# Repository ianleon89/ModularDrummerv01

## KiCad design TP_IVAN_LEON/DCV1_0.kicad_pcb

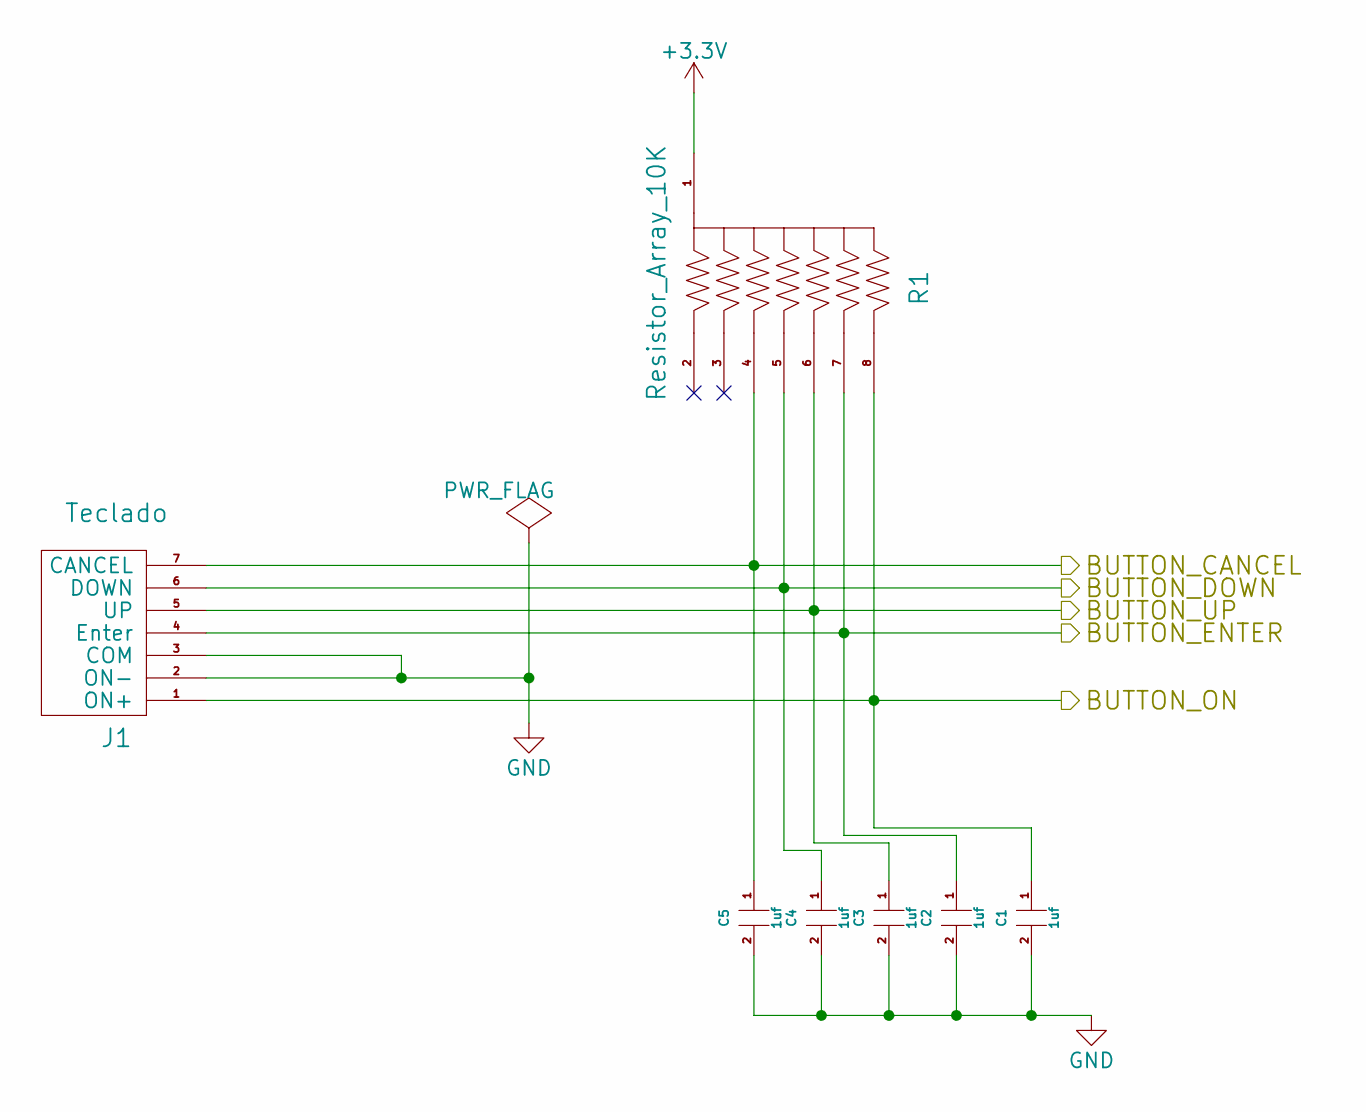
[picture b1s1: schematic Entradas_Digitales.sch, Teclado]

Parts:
C1, C2, C3, C4, C5: 1uf; c_1206; Digikey# 399-1254-2-ND
J1: Teclado; Connector_Molex_PicoBlade_53047-0810; Digikey# WM1737-ND
R1: Resistor_Array_10K; Resistor_Array_SIP8; Digikey# Y1747V0201BA0W-ND

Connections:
+3V3: R1.1; also elsewhere on the board
/Teclado/BUTTON_CANCEL: C5.1, J1.7 (CANCEL), R1.4; also elsewhere on the board
/Teclado/BUTTON_DOWN: C4.1, J1.6 (DOWN), R1.5; also elsewhere on the board
/Teclado/BUTTON_ENTER: C2.1, J1.4 (Enter), R1.7; also elsewhere on the board
/Teclado/BUTTON_ON: C1.1, J1.1 (ON+), R1.8; also elsewhere on the board
/Teclado/BUTTON_UP: C3.1, J1.5 (UP), R1.6; also elsewhere on the board
GND: C1.2, C2.2, C3.2, C4.2, C5.2, J1.2 (ON-), J1.3 (COM); also elsewhere on the board

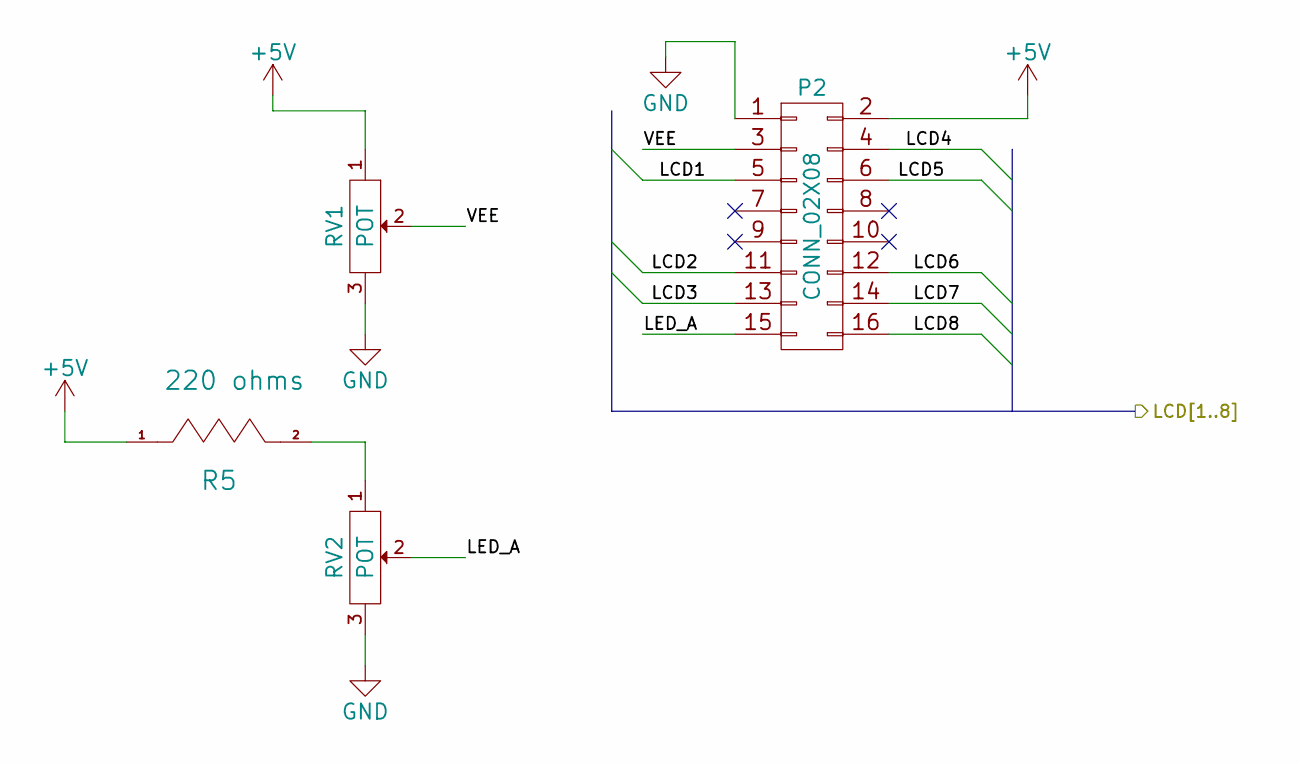
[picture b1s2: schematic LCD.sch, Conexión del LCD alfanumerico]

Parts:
P2: CONN_02X08; Pin_Header_Straight_2x08; Digikey# 952-2268-ND
R5: 220 ohms; Resistor_SMD+THTuniversal_1206_RM10_HandSoldering; Digikey# ERJ-T08J221V-ND
RV1, RV2: POT; Connector_Molex_PicoBlade_53047-0310; Digikey# WM1732-ND

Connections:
+5V: P2.2, R5.1, RV1.1; also elsewhere on the board
/Graphic_Interface/LCD1: P2.5; also elsewhere on the board
/Graphic_Interface/LCD2: P2.11; also elsewhere on the board
/Graphic_Interface/LCD3: P2.13; also elsewhere on the board
/Graphic_Interface/LCD4: P2.4; also elsewhere on the board
/Graphic_Interface/LCD5: P2.6; also elsewhere on the board
/Graphic_Interface/LCD6: P2.12; also elsewhere on the board
/Graphic_Interface/LCD7: P2.14; also elsewhere on the board
/Graphic_Interface/LCD8: P2.16; also elsewhere on the board
/Graphic_Interface/LED_A: P2.15, RV2.2
/Graphic_Interface/VEE: P2.3, RV1.2
GND: P2.1, RV1.3, RV2.3; also elsewhere on the board
unnamed: R5.2, RV2.1

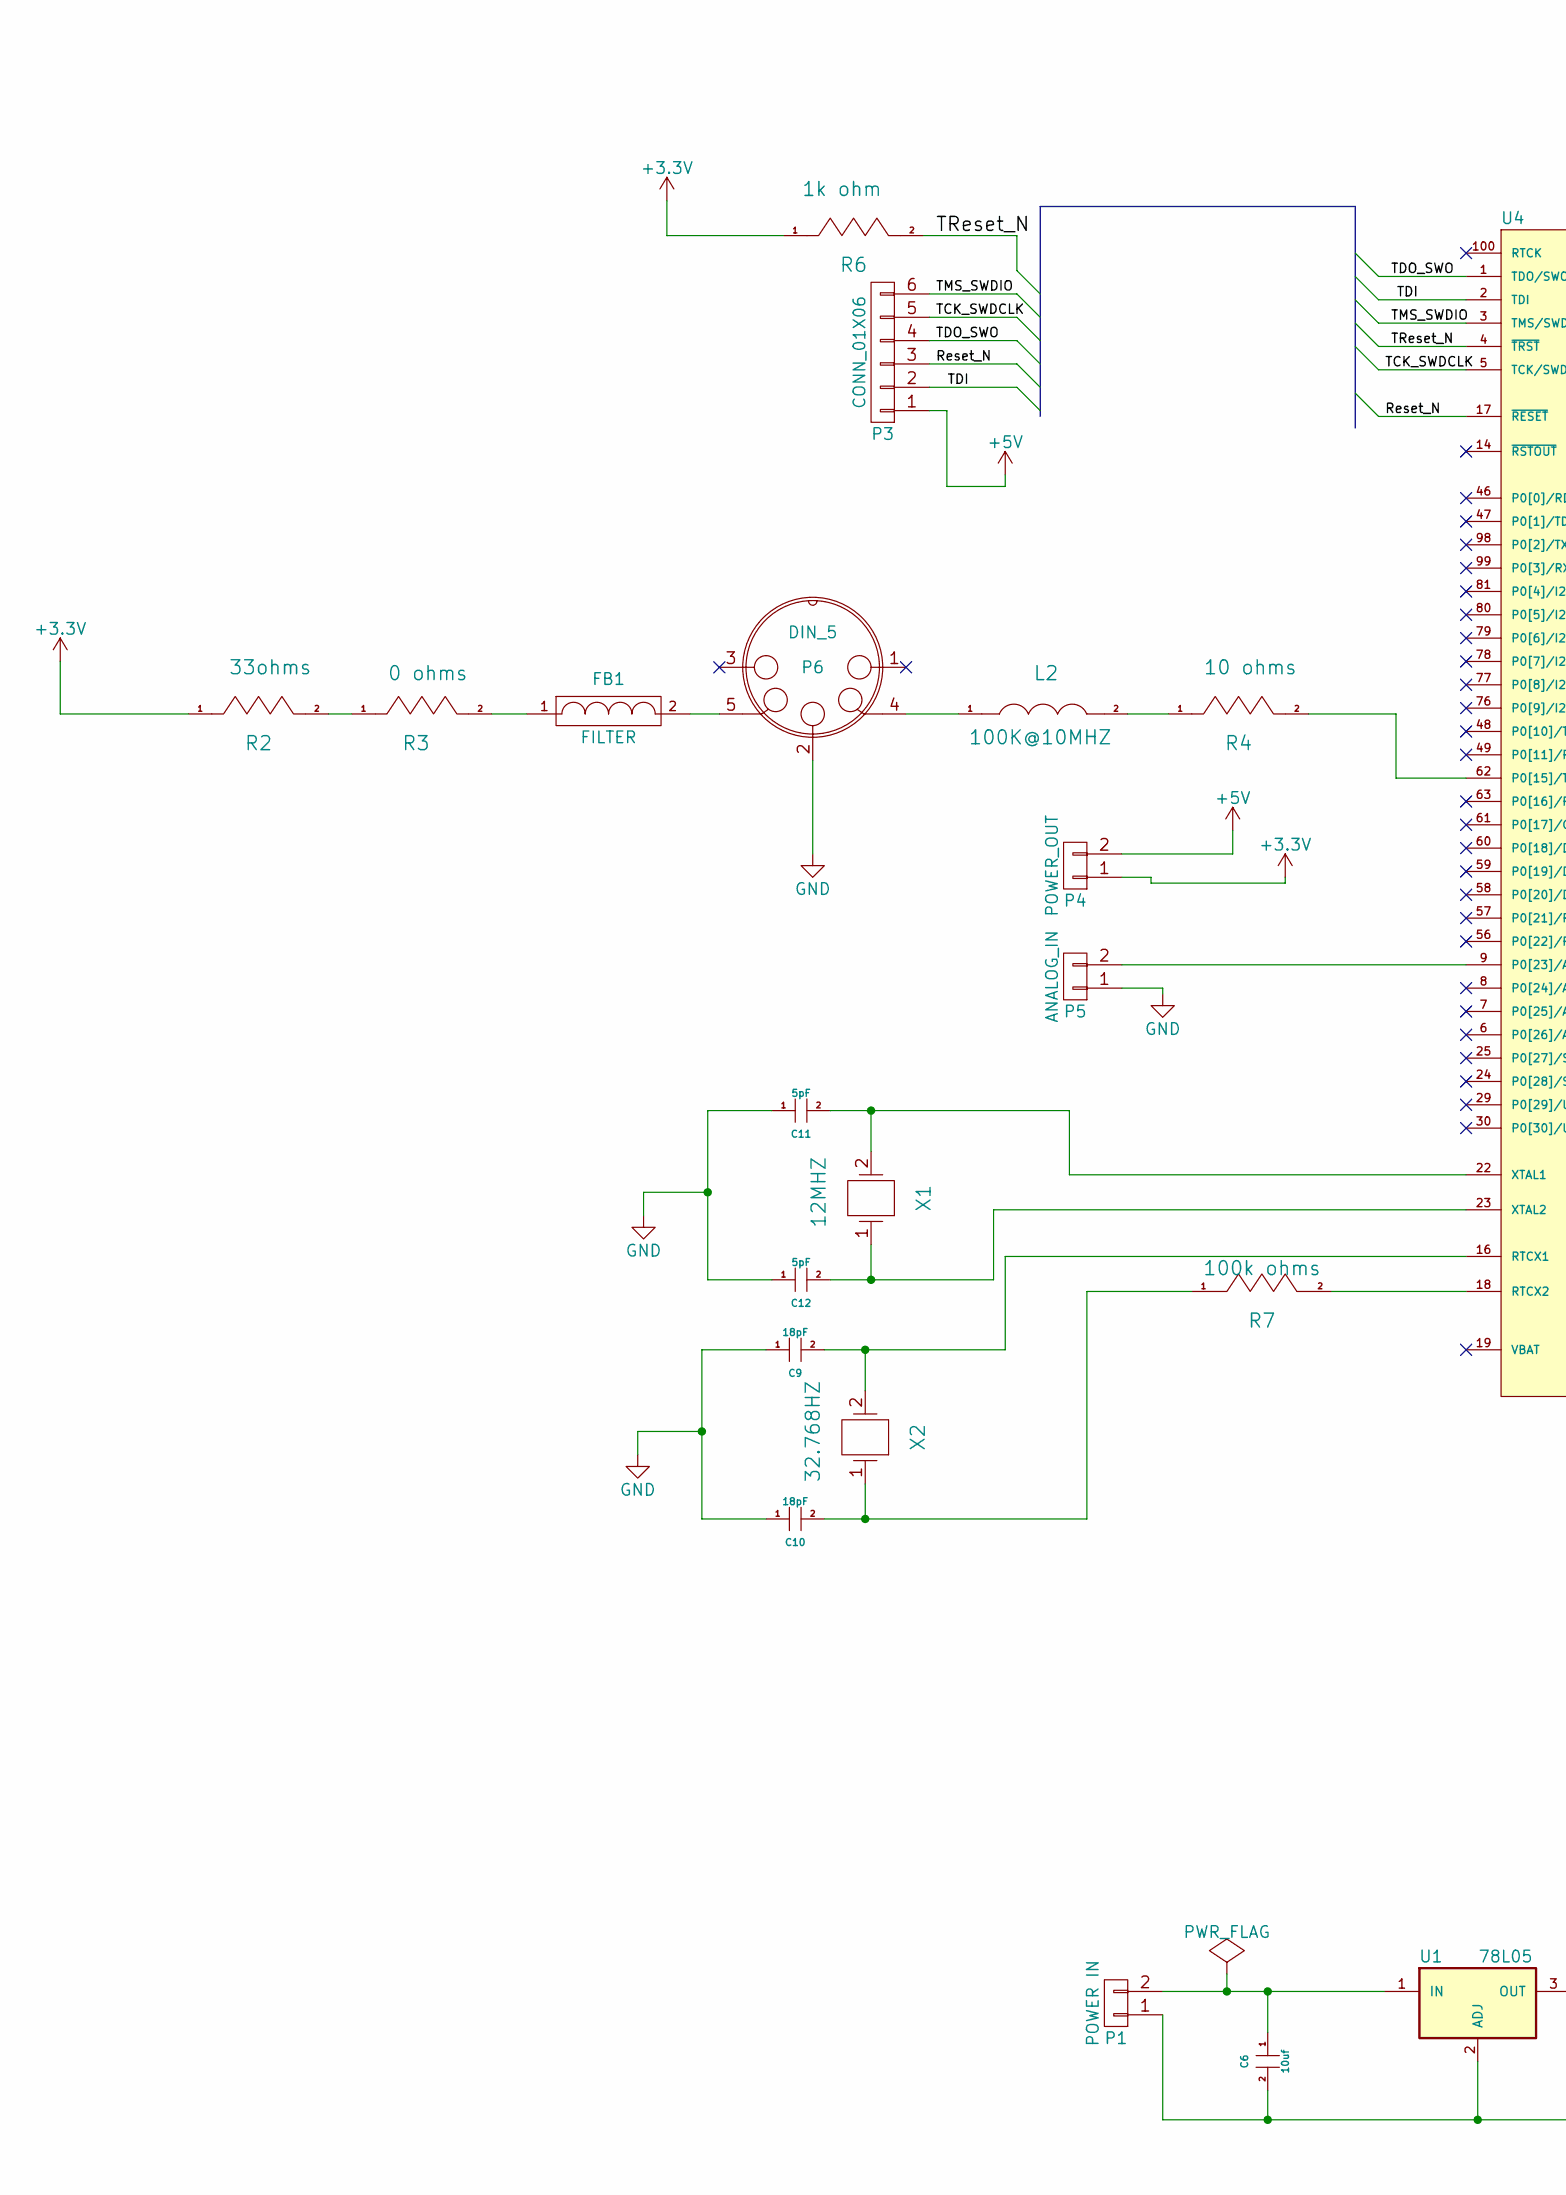
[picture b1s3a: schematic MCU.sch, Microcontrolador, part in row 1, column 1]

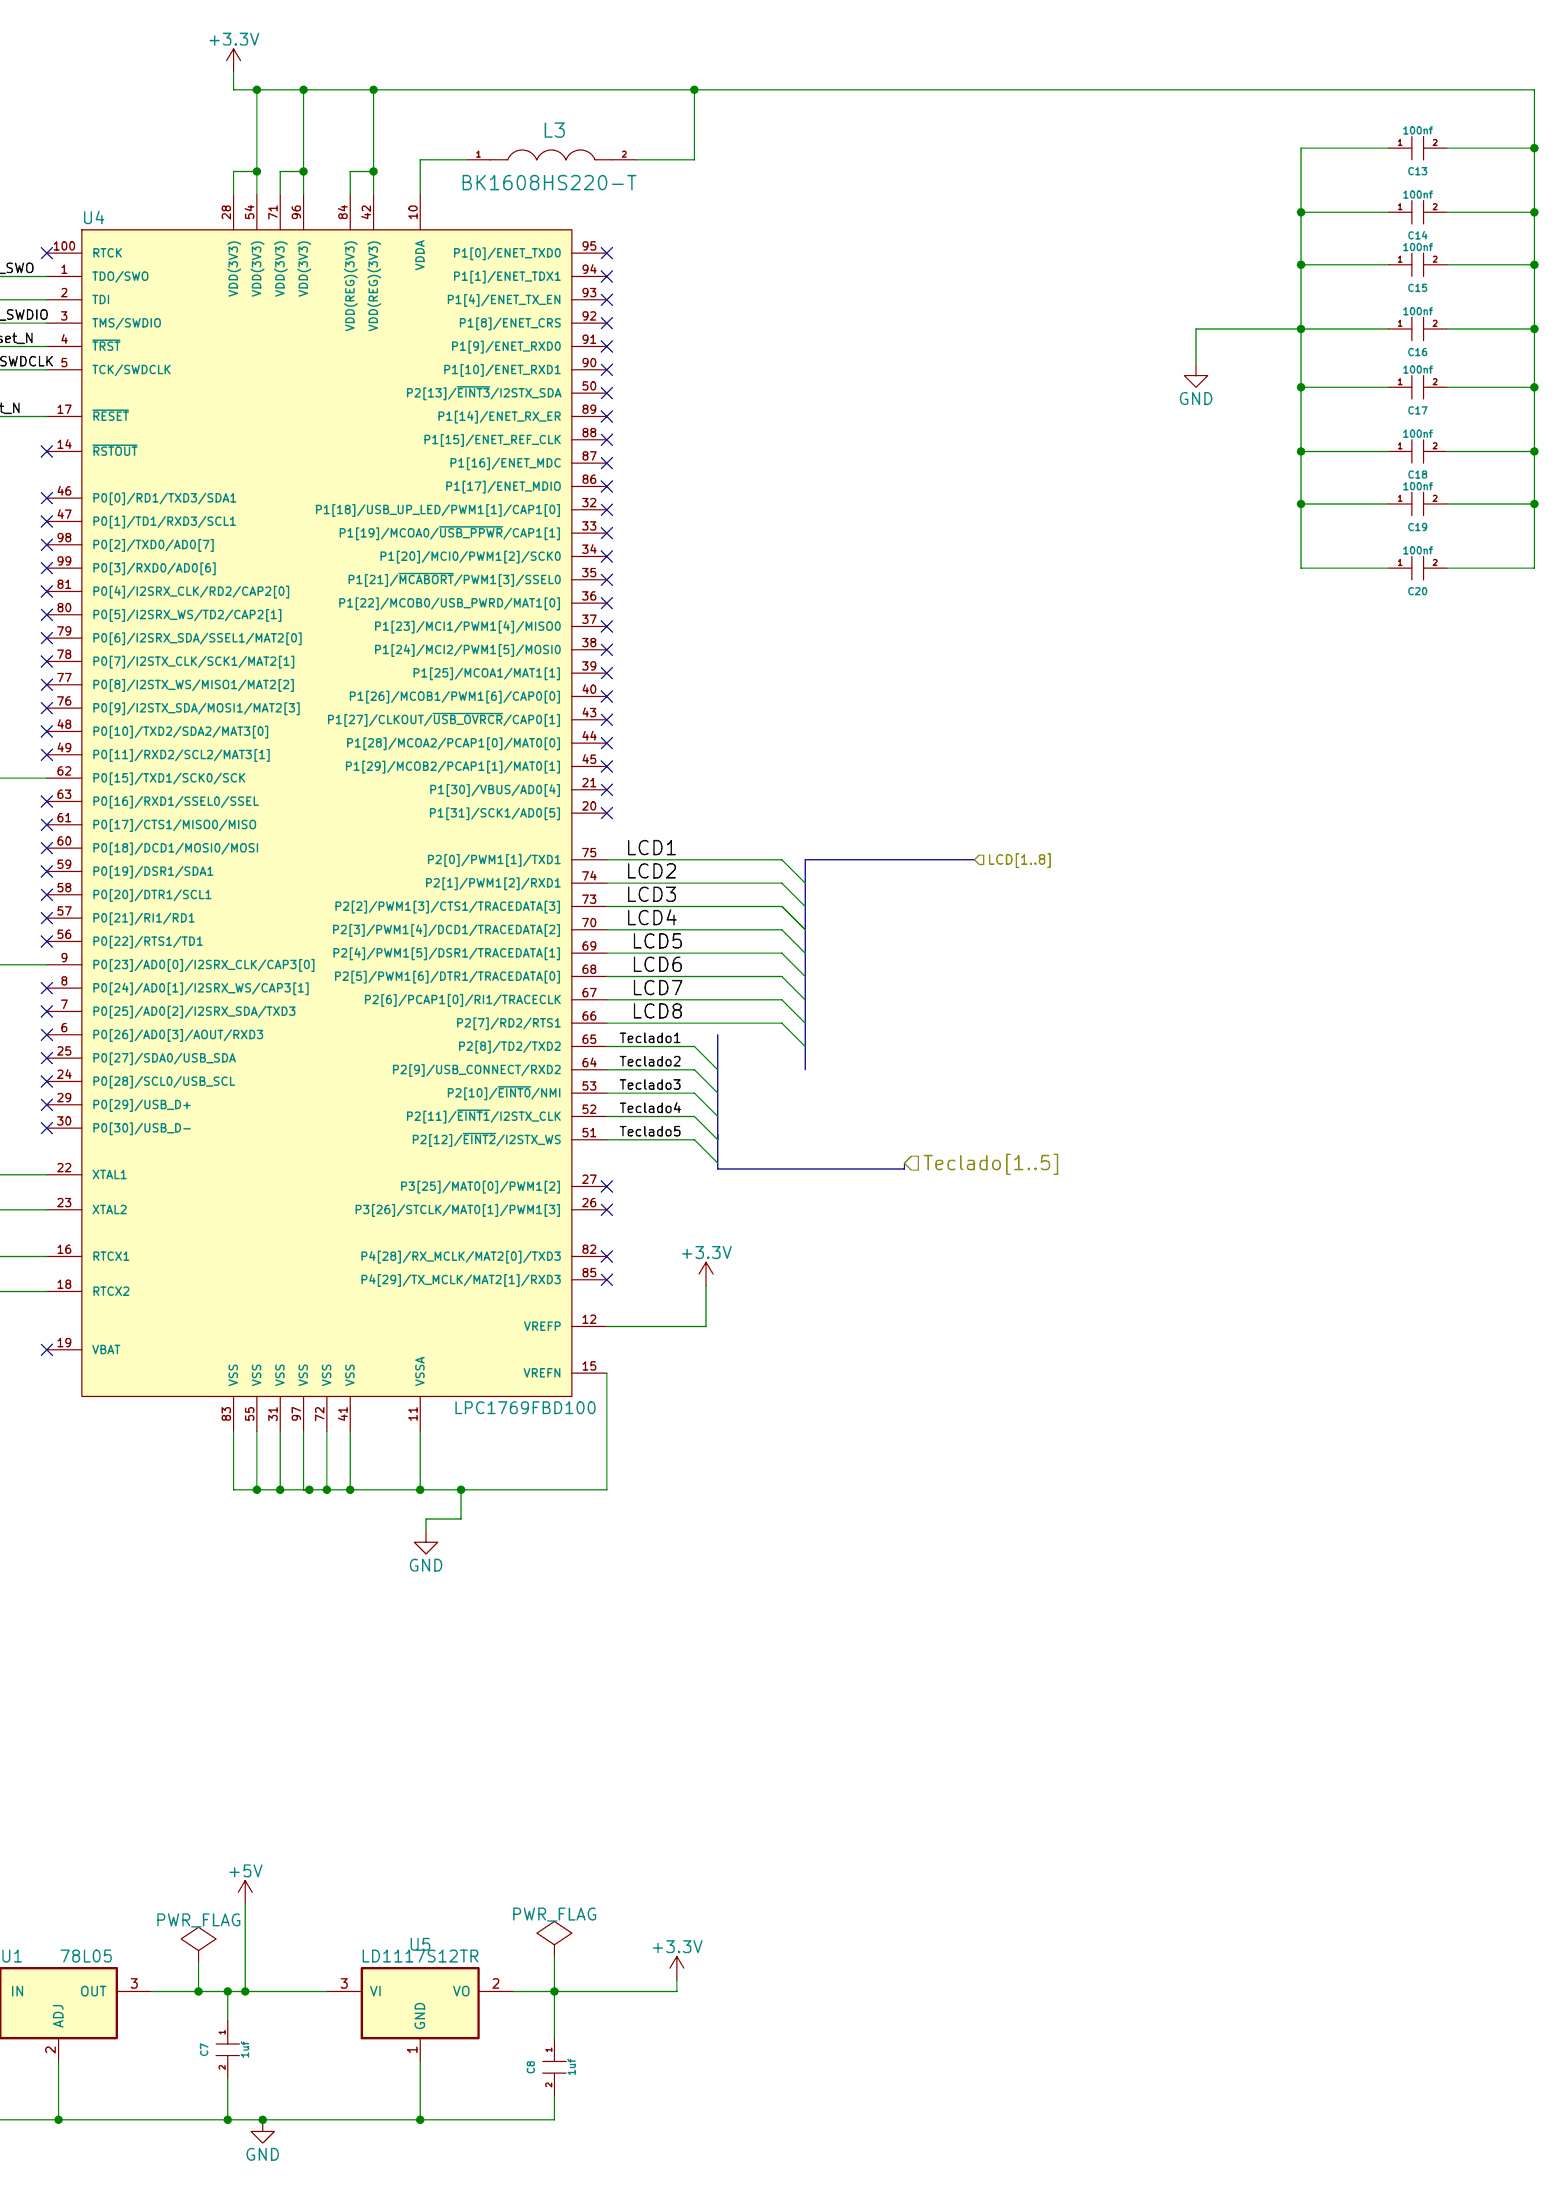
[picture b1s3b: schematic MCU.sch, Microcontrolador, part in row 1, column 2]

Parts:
C6: 10uf; c_1206; Digikey# 490-6473-6-ND
C7, C8: 1uf; c_1206; Digikey# 399-1254-2-ND
C9, C10: 18pF; C_0805_HandSoldering; Digikey# C1206C180D5GACTU-ND
C11, C12: 5pF; C_0805_HandSoldering; Digikey# 12061A5R0CAT2A-ND
C13, C14, C15, C16, C17, C18, C19, C20: 100nf; c_1206; Digikey# 1276-1007-1-ND
FB1: FILTER; Choke_SMD_1206_Standard; Digikey# 732-6713-1-ND
L2: 100K@10MHZ; Choke_SMD_1206_Standard; Digikey# 732-6713-1-ND
L3: BK1608HS220-T; Choke_SMD_1206_Standard; Digikey# 587-1869-2-ND
P1: POWER IN; Connector_Molex_PicoBlade_53047-0210; Digikey# WM1731-ND
P3: CONN_01X06; Connector_Molex_PicoBlade_53047-0610; Digikey# WM1735-ND
P4: POWER_OUT; Connector_Molex_PicoBlade_53047-0210; Digikey# WM1731-ND
P5: ANALOG_IN; Connector_Molex_PicoBlade_53047-0210; Digikey# WM1731-ND
P6: DIN_5; din-5; Digikey# CP-2350-ND
R2: 33ohms; Resistor_SMD+THTuniversal_1206_RM10_HandSoldering; Digikey# 311-33ERTR-ND
R3: 0 ohms; Resistor_SMD+THTuniversal_0805to2512_RM10_HandSoldering; Digikey# 541-2970-6-ND
R4: 10 ohms; Resistor_SMD+THTuniversal_1206_RM10_HandSoldering; Digikey# YAG1337TR-ND
R6: 1k ohm; Resistor_SMD+THTuniversal_1206_RM10_HandSoldering; Digikey# YAG1338TR-ND
R7: 100k ohms; Resistor_SMD+THTuniversal_1206_RM10_HandSoldering; Digikey# HVCB1206FKC100KTR-ND
U1: 78L05; SOT-223; Digikey# 497-1183-2-ND
U4: LPC1769FBD100; LQFP-100_14x14mm_Pitch0.5mm; Digikey# 568-4966-ND
U5: LD1117S12TR; SOT-223; Digikey# 497-4240-2-ND
X1: 12MHZ; Crystal_HC49-U_Vertical; Digikey# X1037-ND
X2: 32.768HZ; Crystal_HC49-U_Vertical; Digikey# CFS-20632768HZBB-ND

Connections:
+3V3: C8.1, C13.2, C14.2, C15.2, C16.2, C17.2, C18.2, C19.2, C20.2, L3.2, P4.1, R2.1, R6.1, U4.12 (VREFP), U4.28 (VDD(3V3)), U4.42 (VDD(REG)(3V3)), U4.54 (VDD(3V3)), U4.71 (VDD(3V3)), U4.84 (VDD(REG)(3V3)), U4.96 (VDD(3V3)), U5.2 (VO); also elsewhere on the board
+5V: C7.1, P3.1, P4.2, U1.3 (OUT), U5.3 (VI); also elsewhere on the board
/Graphic_Interface/LCD1: U4.75 (P2[0]/PWM1[1]/TXD1); also elsewhere on the board
/Graphic_Interface/LCD2: U4.74 (P2[1]/PWM1[2]/RXD1); also elsewhere on the board
/Graphic_Interface/LCD3: U4.73 (P2[2]/PWM1[3]/CTS1/TRACEDATA[3]); also elsewhere on the board
/Graphic_Interface/LCD4: U4.70 (P2[3]/PWM1[4]/DCD1/TRACEDATA[2]); also elsewhere on the board
/Graphic_Interface/LCD5: U4.69 (P2[4]/PWM1[5]/DSR1/TRACEDATA[1]); also elsewhere on the board
/Graphic_Interface/LCD6: U4.68 (P2[5]/PWM1[6]/DTR1/TRACEDATA[0]); also elsewhere on the board
/Graphic_Interface/LCD7: U4.67 (P2[6]/PCAP1[0]/RI1/TRACECLK); also elsewhere on the board
/Graphic_Interface/LCD8: U4.66 (P2[7]/RD2/RTS1); also elsewhere on the board
/MCU /Reset_N: P3.3, U4.17 (~RESET~)
/MCU /TCK_SWDCLK: P3.5, U4.5 (TCK/SWDCLK)
/MCU /TDI: P3.2, U4.2 (TDI)
/MCU /TDO_SWO: P3.4, U4.1 (TDO/SWO)
/MCU /TMS_SWDIO: P3.6, U4.3 (TMS/SWDIO)
/MCU /TReset_N: R6.2, U4.4 (~TRST~)
/Teclado/BUTTON_CANCEL: U4.51 (P2[12]/~EINT2~/I2STX_WS); also elsewhere on the board
/Teclado/BUTTON_DOWN: U4.53 (P2[10]/~EINT0~/NMI); also elsewhere on the board
/Teclado/BUTTON_ENTER: U4.52 (P2[11]/~EINT1~/I2STX_CLK); also elsewhere on the board
/Teclado/BUTTON_ON: U4.65 (P2[8]/TD2/TXD2); also elsewhere on the board
/Teclado/BUTTON_UP: U4.64 (P2[9]/USB_CONNECT/RXD2); also elsewhere on the board
GND: C6.2, C7.2, C8.2, C9.1, C10.1, C11.1, C12.1, C13.1, C14.1, C15.1, C16.1, C17.1, C18.1, C19.1, C20.1, P1.1, P5.1, P6.2, U1.2 (ADJ), U4.11 (VSSA), U4.15 (VREFN), U4.31 (VSS), U4.41 (VSS), U4.55 (VSS), U4.72 (VSS), U4.83 (VSS), U4.97 (VSS), U5.1 (GND); also elsewhere on the board
unnamed: C6.1, P1.2, U1.1 (IN)
unnamed: C9.2, U4.16 (RTCX1), X2.2
unnamed: C10.2, R7.1, X2.1
unnamed: C11.2, U4.22 (XTAL1), X1.2
unnamed: C12.2, U4.23 (XTAL2), X1.1
unnamed: FB1.1, R3.2
unnamed: FB1.2, P6.5
unnamed: L2.1, P6.4
unnamed: L2.2, R4.1
unnamed: L3.1, U4.10 (VDDA)
unnamed: P5.2, U4.9 (P0[23]/AD0[0]/I2SRX_CLK/CAP3[0])
unnamed: R2.2, R3.1
unnamed: R4.2, U4.62 (P0[15]/TXD1/SCK0/SCK)
unnamed: R7.2, U4.18 (RTCX2)

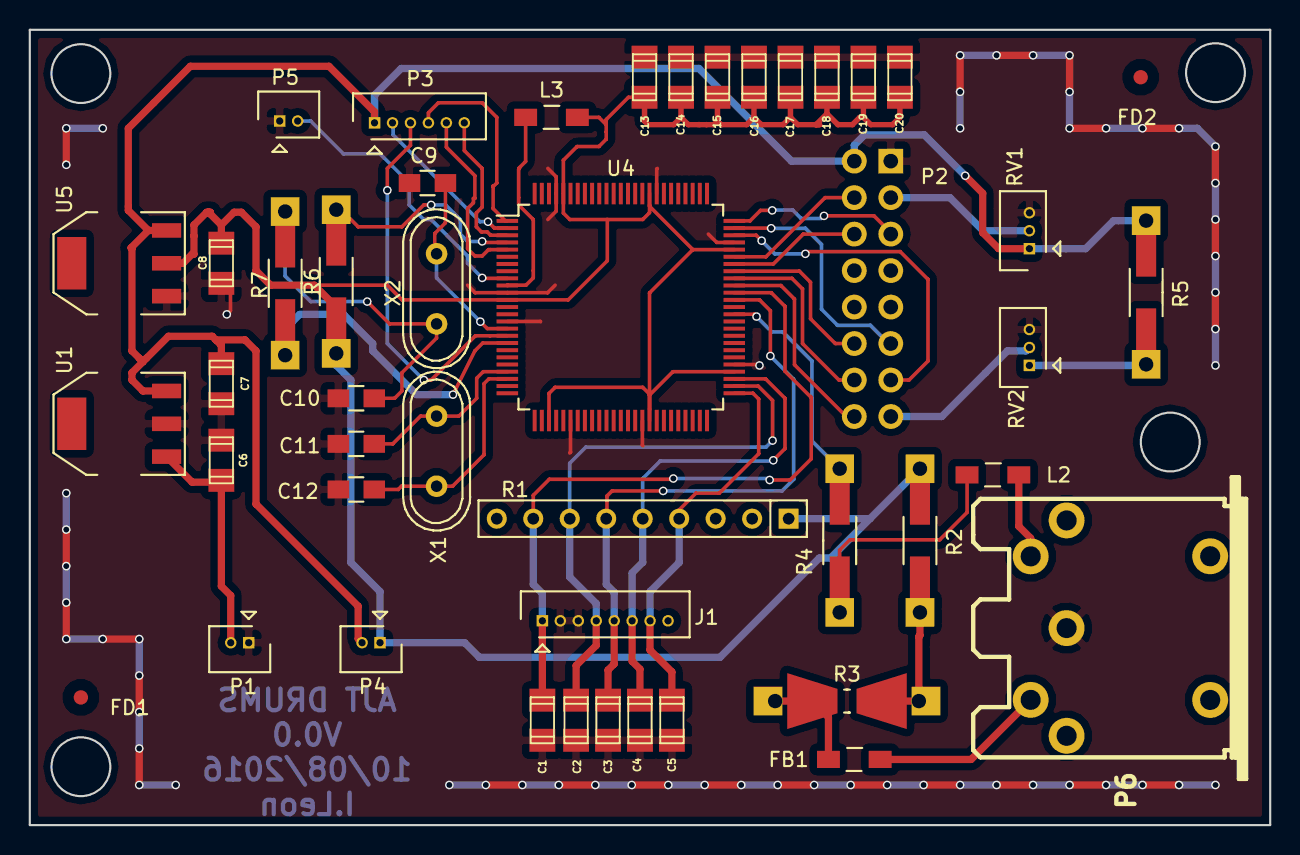
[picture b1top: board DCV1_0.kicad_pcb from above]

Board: 2 copper layers, 86.4 x 55.4 mm, 46 parts (1 on the bottom side), 39 nets.

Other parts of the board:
FD1, FD2: Fiducial_1mm_Dia_2.54mm_Outer_CopperTop

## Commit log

2016-07-27 ReadMe
2016-07-27 Esquematico terminado, falta anadir titulos autor etc y componentes detallados y asociar footprints
2016-08-07 Acabado el pcb, aun no se agrega titulos a los sheets y falta completar cmapos de componenetes
2016-08-10 Creado los gerbers y drill files, puesto los nombres a las hojas
2016-08-11 Agregado codigo digey key en 80% de componentes
2016-08-25 Agregado cambios subrayados en verde descritos en documento Leonv.ods en la carpeta docs
2016-08-25 Agrego Manf y Manf# en todos los componentes
2016-08-25 Agregado fiduciales
2016-08-25 Agregada libreria faltante
2016-08-25 Agregada libreria faltante
2016-08-30 Agregado lo descrito en doc Revision2Leonv, los cambios se describen en el mismo documento
2016-09-02 PCB faltante agregado
